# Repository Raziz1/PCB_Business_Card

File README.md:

# PCB Business Card 💳
The following project is a PCB designed as a business card. This card contains an integrated NFC tag that allows you to share your contact information wirelessly.

<p align="center"><i>Blender Render</i></p>

## NFC Principle 🧲
<b>[NFC (Near Field Communication)](https://www.spiceworks.com/tech/networking/articles/what-is-near-field-communication/)</b> is a group of communication protocols that allows for low speed wireless communication between two electronic devices. 
* NFC communication occurs when both electronic devices are within a distance of 4cm or less. 
* NFC operates at 13.56 MHz on ISO/IEC 18000-3 air interface and at rates ranging from 106 kbit/s to 424 kbit/s.
* The transfer of data in NFC is bi-directional.
* NFC has a setup time of 0.1s. For reference, Bluetooth requires a setup time of 6s.
* NFC utilizes the phenomenon of inductive coupling between two electromagnetic coils.

## NFC IC 📶
THe NFC IC being used in this project is the [NT3H1101W0FTTJ](https://www.digikey.ca/en/products/detail/nxp-usa-inc/NT3H1101W0FTTJ/5347877).
* This chip is an NFC chip designed by NXP. It features I2C communication, energy harvesting, and field detection features. 
* It features 64 bytes of SRAM and 1kB of EEPROM memory. We can use the onboard memory to stored a personal website link for the user device to retrieve when communicating with the IC.
* Lastly with this chip, we can utilize the induced current to power the chip (i.e., energy harvesting).
* We can program the IC through the [NFC TagWriter by NXP](https://play.google.com/store/apps/details?id=com.nxp.nfc.tagwriter&hl=en_GB) app.

## NFC Equivalent Circuit
The internet has a plethora of resources for antenna design. The two sources I will be referring to for this design are:
* [AN11276 - NXP Community](https://community.nxp.com/pwmxy87654/attachments/pwmxy87654/nfc/6155/1/AN11276.pdf)
* [AN2972 Application note How to design an antenna for dynamic NFC tags](https://www.st.com/resource/en/application_note/an2972-how-to-design-an-antenna-for-dynamic-nfc-tags-stmicroelectronics.pdf)

The figure below shows the equivalent electrical circuits of the dynamic NFC tag and its antenna.

The above circuit can be simplified into an equivalent RLC circuit.

### Resonance Frequency
Based on the simplified RLC circuit we can determine the resonant frequency. 
* Resonance frequency is the frequency (in hertz) in which a signal or power level can be carried, or couple from one device to another with no power or signal loss "ideally".
* $f_R=\frac{1}{2\cdot \pi \cdot \sqrt{L_{pc}\cdot C_{pl}}}$
    * $C_{pl}=C_{tun}+C_{ant}$

We know that for an NFC tag, the desired frequency is 13.56 MHz. We also know that the IC's parallel capacitance is 50 pF (from the datasheet). <i>Ignore the parasitic capacitance of the antenna for now; we will come back to that</i>. Based on this information, we can work backwards to determine the required inductance of the antenna.

$f_R=\frac{1}{2\cdot \pi \cdot \sqrt{L_{pc}\cdot C_{pl}}}$

$L_{pc}=\frac{1}{C_{pl}\left(2\pi f_R\right)^2}$

$L_{pc}=\frac{1}{5\cdot 10^{-11}\left(2\pi \cdot 13560000\right)^2} = 0.00000275518$

$L_{pc}=0.00000275518\:H=\:2.75518\:uH$

## Antenna Design 📡
We can now design an NFC antenna based on the desired inductance calculated above. To design the antenna I referred to various resources to confirm my calculations. 

### NXP Spiral Antenna Calculation
The [AN11276 NTAG Antenna Design Guide](https://community.nxp.com/pwmxy87654/attachments/pwmxy87654/nfc/6155/1/AN11276.pdf) provides the following information to design an antenna. 

<p align="center"><i>NXP Class 4 Antenna Design Recommendation</i></p>

<p align="center"><i>NXP Round Antennas Formula</i></p>

I utilized the [Antenna_Shape_Calculator](/Resource_Documents/Antenna_Shape_Calculator.xlsx) excel document to calculate the geometric parameters. They were as follows:
* $D_0 = 41mm$
* $t = 35um$
* $w = 300um$
* $g = 300um$
* $Nant = 6\:turns$
* $L_{calc} = 2.754uH$

### STM Spiral Antenna Calculation
The [AN2972 Application note](https://www.st.com/resource/en/application_note/an2972-how-to-design-an-antenna-for-dynamic-nfc-tags-stmicroelectronics.pdf) provides the following information to design an antenna. 

<p align="center"><i>STM Spiral Antenna Design</i></p>

<p align="center"><i>STM Spiral Antennas Formula</i></p>

I utilized the [Antenna_Shape_Calculator](/Resource_Documents/Antenna_Shape_Calculator.xlsx) excel document to calculate the geometric parameters. They were as follows:
* $r_{in} = 17.5mm$
* $r_{out} = 20.5mm$
* $Nant = 6\:turns$
* $L_{calc} = 2.766uH$

### Missing Parameters 
We are not quite ready to complete the design. Looking back at the equivalent circuit, we are still missing a few parameters: antenna capacitance, antenna resistance, and the NFC IC resistance. Typically, these parameters are determined by measuring the actual physical circuit design. For a guide on how to measure these parameters, check out the following link: --> [Guide to designing antennas for the NTAG I2C plus](https://community.nxp.com/t5/NXP-Designs-Knowledge-Base/Guide-to-designing-antennas-for-the-NTAG-I2C-plus/ta-p/1104729).  Nevertheless, we can make some rough estimations by utilizing various tools.

* Antenna resistance - By using a parasitic resistance tool in KiCad, we can calculate this parameter. According to the tool, the parasitic resistance was 1.17 ohms. 
* Antenna capacitance - By utilizing the [NXP NFC Antenna Tool](https://community.nxp.com/t5/NFC/bd-p/nfc/page/4?_gl=1*gmz3or*_ga*NzkyMDk1NzYwLjE3MTEwNTg3NTE.*_ga_WM5LE0KMSH*MTcxMTU1MzAwMS4xMy4wLjE3MTE1NTMwMDEuMC4wLjA.) we can roughly estimate this parameter. This tool does not support spiral designs, but we can use the rectangular design to estimate this parameter. According to the tool, the parasitic capacitance was 1.9 pF.
* NFC IC Resistance - Assuming the voltage should drop entirely across the IC, we can consider this resistance to be infinitely large. For our purposes, we will estimate it to be 100k ohms.

<p align="center"><i>NXP NFC Antenna Tool</i></p>

## Simulation
We can now work our way backwards to verify the parameters we calculated above. By rebuilding the equivalent circuit with these parameters in LTSpice, we can verify the resonance frequency. According to the simulation below, the resonance frequency is 13.35 MHz. This should be adequate for NFC; alternatively, we can target an inductance of 2.5-2.6 uH to achieve a resonance frequency that is closer to 13.56 MHz. Furthermore, an optional tuning capacitor can be added to get closer to 13.56 MHz.

<p align="center"><i>LTSpice Simulation</i></p>

I decided to rerun the simulation and redesign the antenna parameters ($D_0 = 39mm$) to target an inductance of 2.576uH. This gives us more headroom to account for any imperfections in the manufacturing process. This allows us to use a tuning capacitor to bring the resonance frequency down and closer to 13.56 MHz.  

<p align="center"><i>LTSpice Simulation with Tuning Capacitor</i></p>

### Electromagnetic Simulation 🧲
Antennas are typically simulated using electromagnetic simulation software to predict and optimize their real-world performance. A variety of tools are available, such as:
* Ansys HFSS/Maxwell - The student edition is free but has limitations
* Solidworks CST Microwave -  The student edition is free but has limitations
* openEMS
* MATLAB Antenna Toolbox

For this design, I chose to work with MATLAB’s Antenna Toolbox and RF Toolbox, as I did not yet have the experience to effectively use industry-grade tools like HFSS or CST.

#### MATLAB Antenna Toolbox

<p align="center"><i>MATLAB 3D Radiation Pattern</i></p>

After spending several days experimenting with the MATLAB script from the repository, I was unsuccessful in reproducing a clear resonance at 13.56 MHz. I tried designing the antenna directly in the Antenna Toolbox, carefully defining spiral coil parameters, trace width, spacing, and substrate properties. I also attempted to import the PCB layout into the PCB Antenna Toolbox using the gerber files of the actual NFC coil. Despite these efforts, the desired resonance could not be achieved. Following a discussion with [Umar on the MATLAB Answers forum](https://www.mathworks.com/matlabcentral/answers/2180231-matlab-nfc-antenna-simulation?s_tid=srchtitle), it was clarified that the limitation lies in the software itself for this specific application:

>* *"MATLAB’s Antenna Toolbox is designed for far-field radiation analysis, not near-field inductive coupling. NFC, however, operates in the reactive near-field, where antennas behave as coupled inductors rather than radiating elements. The S11 parameters calculated in MATLAB inherently assume radiation losses, which do not accurately represent NFC coil physics."* *

At this stage, Umar provided a toolbox-free MATLAB script that verified the design using RF first principles, which is available in the repository. The script addressed the following calculations:
* Inductance using Wheeler’s formula (adapted to spiral coil + substrate corrections)
* AC + DC resistance including skin effect and dielectric loss
* Impedance of the NFC IC (modeled as parallel R + C)
* Combined system impedance and S11 over a narrower frequency sweep
* Determination of resonant frequency (by finding minimum imaginary part)
* Computation of required tuning capacitance
* Quality factor (Q), VSWR, bandwidth, return loss, Smith chart, etc.
* Using this method, Umar was able to detect a resonance around 11.81 MHz (≈ 12.9% error relative to target) with realistic inductance, resistance, and matching parameters. 

<p align="center"><i>Umar Script Output</i></p>

## PCB Design
For the final design of the antenna I ended up settling on the following parameters:
* $D_0 = 39mm$
* $t = 35um$
* $w = 300um$
* $g = 300um$
* $Nant = 6\:turns$
* $L_{calc} = 2.576uH$
* $R_{ant} = 1.17\:ohms$
* $C_{ant} = 2pF$
* $Simulated\:resonance\:frequency:\:13.75 MHz$ 
    * *Without Tuning Capacitor*

For the schematic, I borrowed the idea of an LED indicator for the energy harvesting circuit from the [PCB Business Card With NFC](https://www.instructables.com/PCB-Business-Card-With-NFC/). The capacitor is to guarantee operation during RF communication. The resistor value was chosen to limit the current going through the LED. The value was determined by using the following equation:
* $R\:=\:\frac{V_{CC}-V_{LED}}{I_{LED}}=\frac{3.3-2}{0.02} = 65Ω$

<p align="center"><i>Schematic Design</i></p>

<p align="center"><i>PCB Design</i></p>

## Final BOM 📃
* [NT3H1101W0FTTJ - IC RFID TRANSP 13.56MHZ 8TSSOP](https://www.digikey.ca/en/products/detail/nxp-usa-inc/NT3H1101W0FTTJ/5347877)
* [150060VS75000 - LED GREEN CLEAR 0603 SMD](https://www.digikey.ca/en/products/detail/w%C3%BCrth-elektronik/150060VS75000/4489906)
* [C0603C224J4REC7867 - CAP CER 0603 220NF 16V X7R 5%](https://www.digikey.ca/en/products/detail/kemet/C0603C224J4REC7867/8643651)
* [CRCW060364R9FKEA - RES SMD 64.9 OHM 1% 1/10W 0603](https://www.digikey.ca/en/products/detail/vishay-dale/CRCW060364R9FKEA/1174533)
* [GRM0335C1E1R5BA01D - CAP CER 1.5PF 25V C0G/NP0 0201 (0603 Metric)](https://www.digikey.ca/en/products/detail/murata-electronics/GRM0335C1E1R5BA01D/4358584)

## Manufacturing 🪛
I ordered the board through PCBWay by using the [KiCAD plugin](https://www.pcbway.com/blog/News/PCBWay_Plug_In_for_KiCad_3ea6219c.html). I assembled and soldered the components on the board myself. 

For the PCBWay specification selection I chose the following options:
* Layers: 2
* Material: FR-4
* FR4-TG: TG130-140
* Thickness: 1.6mm
* Min track/spacing: 5/5mil
* Solder mask: Green
* Silkscreen: White
* Edge connector: No
* Surface finish: HASL with lead
* Via process: Tenting vias
* Finished copper: 1 oz Cu
* Remove product Num: No

<p align="center"><i>Final Product</i></p>

## Programming 💻
Lastly, I programed the IC through the [NFC TagWriter by NXP](https://play.google.com/store/apps/details?id=com.nxp.nfc.tagwriter&hl=en_GB) app.

<p align="center"><i>PCB in Action!</i></p>

> [!CAUTION]
> ### iPhone Compatibility & Energy Harvesting Limit
>
> During real-world testing, this card worked reliably on Android devices but failed to trigger background NFC reading on iPhones.
>
> * **Polling Fields:** iPhones emit low-energy, brief polling bursts to conserve battery, whereas many Android phones broadcast significantly stronger, higher-energy continuous RF fields.
> * **Energy Starvation:** When attempting to harvest energy from an iPhone, the on-board LED circuit drew too much current. This collapsed the harvested voltage rail before the NT3H1101’s digital core could boot and complete its initial communication handshake.
>
> #### Circuit Current Consumption
> Based on the populated components ($R = 64.9\ \Omega$ and a green LED with $V_f \approx 2.0\text{ V}$), the branch demands:
>
> $$I_{LED} = \frac{V_{OUT} - V_{LED}}{R} = \frac{3.3\text{ V} - 2.0\text{ V}}{64.9\ \Omega} \approx 20\text{ mA}$$
>
> #### Datasheet Limit
> According to the NXP NT3H1101/1201 datasheet:
>
> > *"The voltage and current from the energy harvesting depend on various parameters, such as the strength of the RF field, the tag antenna size, or the distance from the NFC device. At room temperature, NTAG I2C could provide typically 5 mA at 2 V on the VOUT pin with an NFC Phone.*
> >
> > *Operating NTAG I2C in energy harvesting mode requires a number of precautions:*
> > * *A significant capacitor is needed to guarantee operation during RF communication. The total capacitor between VOUT and GND shall be in the range of 150nF to 200 nF.*
> >
> > *Note that increasing the output current on the Vout decreases the RF communication range."*
>
> Because the IC typically delivers only up to **5 mA at 2 V** under smartphone coupling, an active load demanding **~20 mA** collapses the harvested rail on lower-power emitters like iPhones.
>
> **Fix:** Leaving the LED/resistor unpopulated (or increasing the resistor to $\ge 1\text{--}2\text{ k}\Omega$ to limit current below $1\text{ mA}$) immediately restores instant background read compatibility on iPhones.

## Characterization 🔬
Finally, I wanted to characterize the response of the circuit using my Analog Discovery 2 - USB oscilloscope. In particular, I aimed to characterize and visualize the difference in responses when the circuit had and didn't have a tuning capacitor.

### No Tuning Capacitor

The first order of business was to utilize the network analyzer feature on the Analog Discovery 2. By attaching the wave generator on one end of the antenna and probing on the other we could sweep through various frequencies and observe the circuits response.

<p align="center"><i>Network Analyzer</i></p>

The above graph describes the S11 parameter, which represents the return loss of a device, indicating how much of the input power supplied to the device reflects back to the input port. We observe that at 14 MHz, the graph dips to a gain of -44.9 dB. This indicates that at 14 MHz, the magnitude of the reflected signal is lower than the magnitude of the incident signal. This implies that the antenna is absorbing the incident energy rather than reflecting it back towards the source. This response closely matches what we simulated previously in LTspice and MATLAB. For an NFC antenna, this behavior is desirable at 13.56 MHz. We can generate a graph with a dip closer to 13.56 MHz by including the tuning capacitor!

<p align="center"><i>Spectrum Analyzer</i></p>

Lastly, during the operation of the circuit, we can utilize the spectrum analyzer to observe the magnitude of the incoming signal. Keep in mind that this circuit doesn't contain a tuning capacitor. This was achieved by probing both ends of the antenna. Once a phone was brought within operating distance, we could see that the antenna contained a signal with a magnitude of 12.37 dB at 13.56 MHz.

### Tuning Capacitor Included (3.9pF)

By introducing a tuning capacitor with a value of 3.9pF, I was able to adjust the circuit's response to achieve resonance closer to the NFC standard of 13.56 MHz. Below is the graph produced by the network analyzer. We can see that this time the graph dips at a frequency of 13.555 MHz with a gain of -44.34 dB.

<p align="center"><i>Network Analyzer</i></p>

<p align="center"><i>Spectrum Analyzer</i></p>

Utilizing the same process as the previous spectrum analysis, we can observe that the antenna contained a signal with a magnitude of 12.494 dB at 13.562 MHz.

### Poorly Tuned NFC Antenna
By introducing a really large tuning capacitor with a value of 15pF, we can adjust the circuit's response to achieve resonance at 12.5 MHz. Given the poorly tuned antenna, we expect to either see that the NFC capabilities cease to work or that the magnitude of the NFC signal is extremely weak. We can quantify this by utilizing the same spectrum analysis technique as used in the previous examples.

<p align="center"><i>Spectrum Analyzer of Poorly Tuned Antenna</i></p>

With the poorly tuned antenna, the NFC capabilities continued to work. However, it did require the phone to be slightly closer to the antenna. Additionally, based on the above graph, we can see that the magnitude of the NFC signal (13.56MHz) is significantly weaker than in previous examples.

## NFC Protocol
By utilizing the Analog Discovery 2 oscilloscope feature, I was able to capture a snippet of an NFC transmission. This was done by probing the antenna during NFC operation. The NFC protocol is extremely complicated, and therefore, it is difficult to decipher what this transmission is. You can click on the following link to learn more about the [NFC transmission protocol](https://scdn.rohde-schwarz.com/ur/pws/dl_downloads/dl_application/application_notes/1ma182/1MA182_5E_NFC_WHITE_PAPER.pdf).

<p align="center"><i>NFC Transmission</i></p>

# Resources
* [Guide to designing antennas for the NTAG I2C plus
](https://community.nxp.com/t5/NXP-Designs-Knowledge-Base/Guide-to-designing-antennas-for-the-NTAG-I2C-plus/ta-p/1104729#toc-hId--56223682)
* [PN7160 antenna design and matching guide](https://www.nxp.com/docs/en/application-note/AN13219.pdf)
* https://github.com/shawnalexsony/Business_Card_PCB/tree/main
* [PCBWAY Custom Design Rules Templates](https://www.pcbway.com/pcb_prototype/PCB_Design_Rule_Check.html?currency=1)

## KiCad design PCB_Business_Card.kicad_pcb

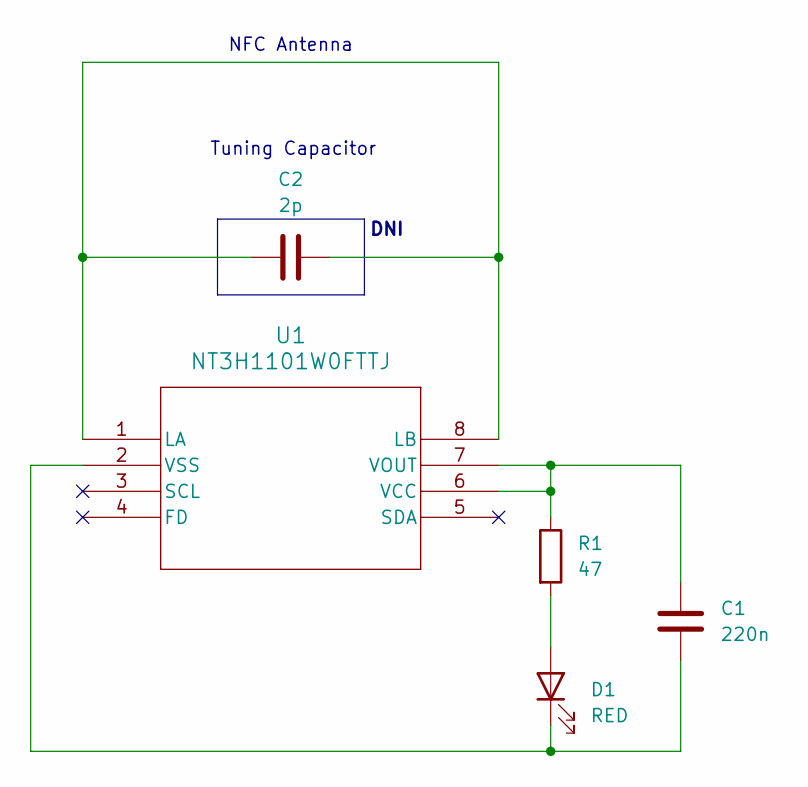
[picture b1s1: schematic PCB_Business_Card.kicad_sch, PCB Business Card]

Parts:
C1: 220n; C_0603_1608Metric
C2: 2p; C_0603_1608Metric
D1: RED; LED_0603_1608Metric
R1: 47; R_0603_1608Metric
U1: NT3H1101W0FTTJ; TSSOP8_SOT505-1_NXP

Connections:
unnamed: D1.2 (A), R1.2
unnamed: C1.2, D1.1 (K), U1.2 (VSS)
unnamed: C2.1, C2.2, U1.1 (LA), U1.8 (LB)
unnamed: C1.1, R1.1, U1.6 (VCC), U1.7 (VOUT)

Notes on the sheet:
DNI
NFC Antenna
Tuning Capacitor

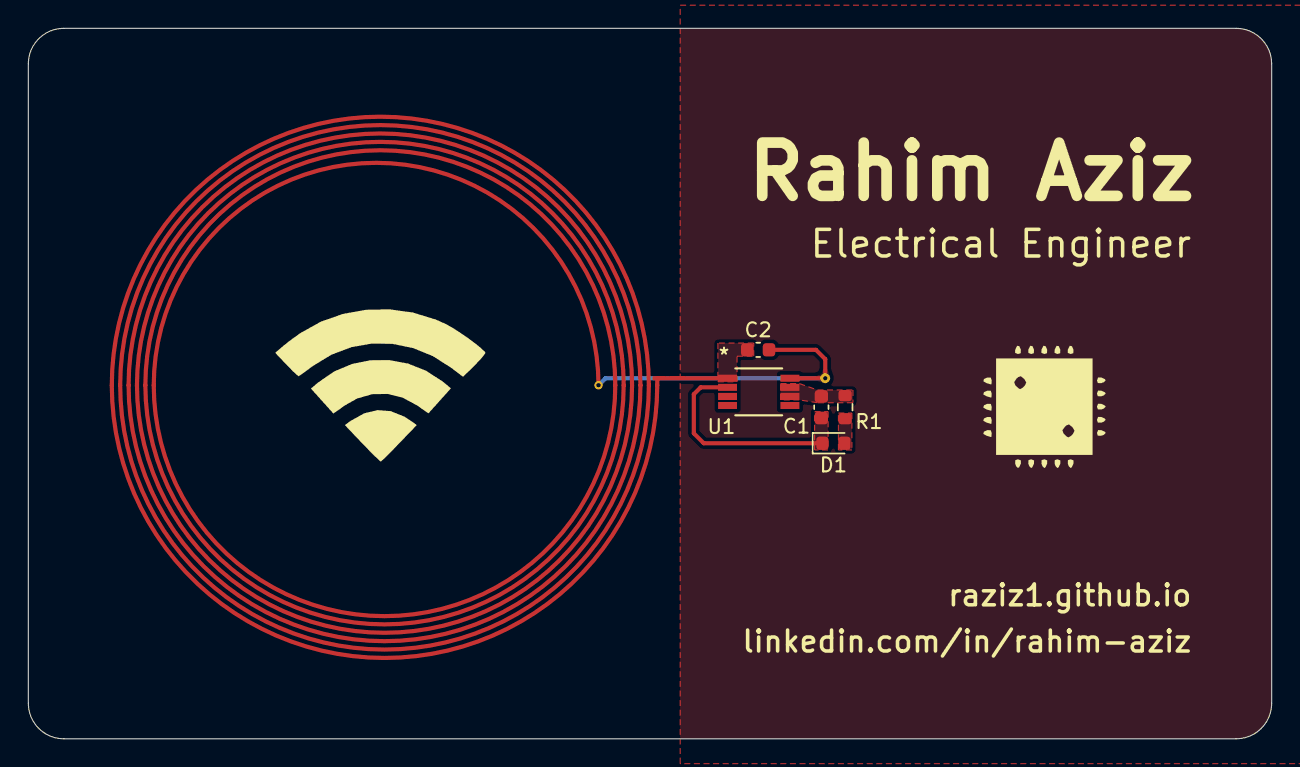
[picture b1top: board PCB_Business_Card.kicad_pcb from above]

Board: 2 copper layers, 88.9 x 50.8 mm, 5 parts (0 on the bottom side), 4 nets.

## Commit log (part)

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2024-04-03 Updated Render
2024-04-04 Generated Gerber files
2024-04-04 Added tuning capacitor
2024-04-04 Updated README.md file
2024-04-12 Added pictures of final product
2024-04-13 Spectrum Analysis
2024-04-14 Circuit Response
    * Network analyzer graph
    * Spectrum analyzer graph
2024-04-14 Updated LED resistor
2024-04-14 Updated untuned spice simulation
2024-04-15 Tuning capacitor results
2024-04-16 NFC transmission & Poorly tuned antenna
2024-04-18 Updated IC image
2025-09-29 Updated EM simulation
